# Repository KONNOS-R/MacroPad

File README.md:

Making a multipurpose Macro Pad for photo, video and audio editing for the blueprint "hackpad" project on hackclub.

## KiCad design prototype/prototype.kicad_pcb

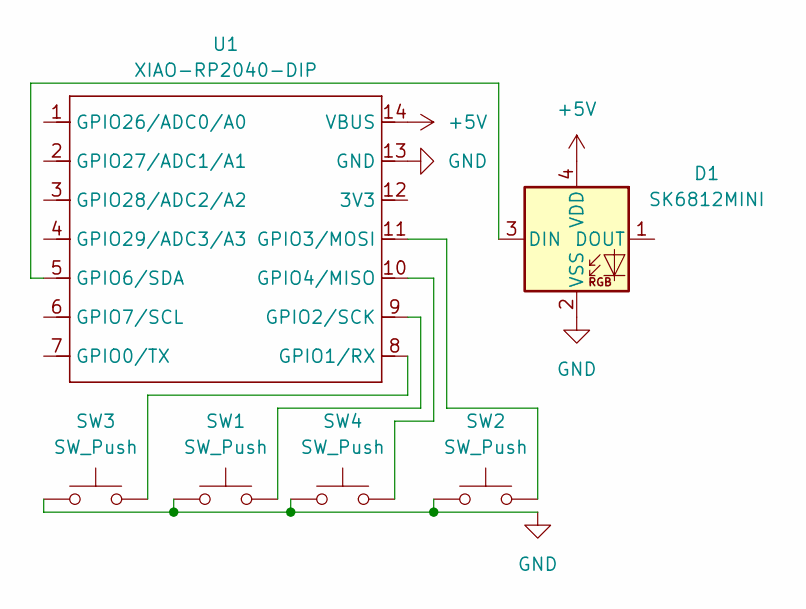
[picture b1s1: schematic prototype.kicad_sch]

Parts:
D1: SK6812MINI; LED_SK6812MINI_PLCC4_3.5x3.5mm_P1.75mm
SW1, SW2, SW3, SW4: SW_Push; SW_Cherry_MX_1.00u_PCB
U1: XIAO-RP2040-DIP

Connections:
+5V: D1.4 (VDD), U1.14 (VBUS)
GND: D1.2 (VSS), SW1.1, SW2.1, SW3.1, SW4.1, U1.13 (GND)
unnamed: D1.3 (DIN), U1.5 (GPIO6/SDA)
unnamed: SW3.2, U1.8 (GPIO1/RX)
unnamed: SW1.2, U1.9 (GPIO2/SCK)
unnamed: SW2.2, U1.11 (GPIO3/MOSI)
unnamed: SW4.2, U1.10 (GPIO4/MISO)

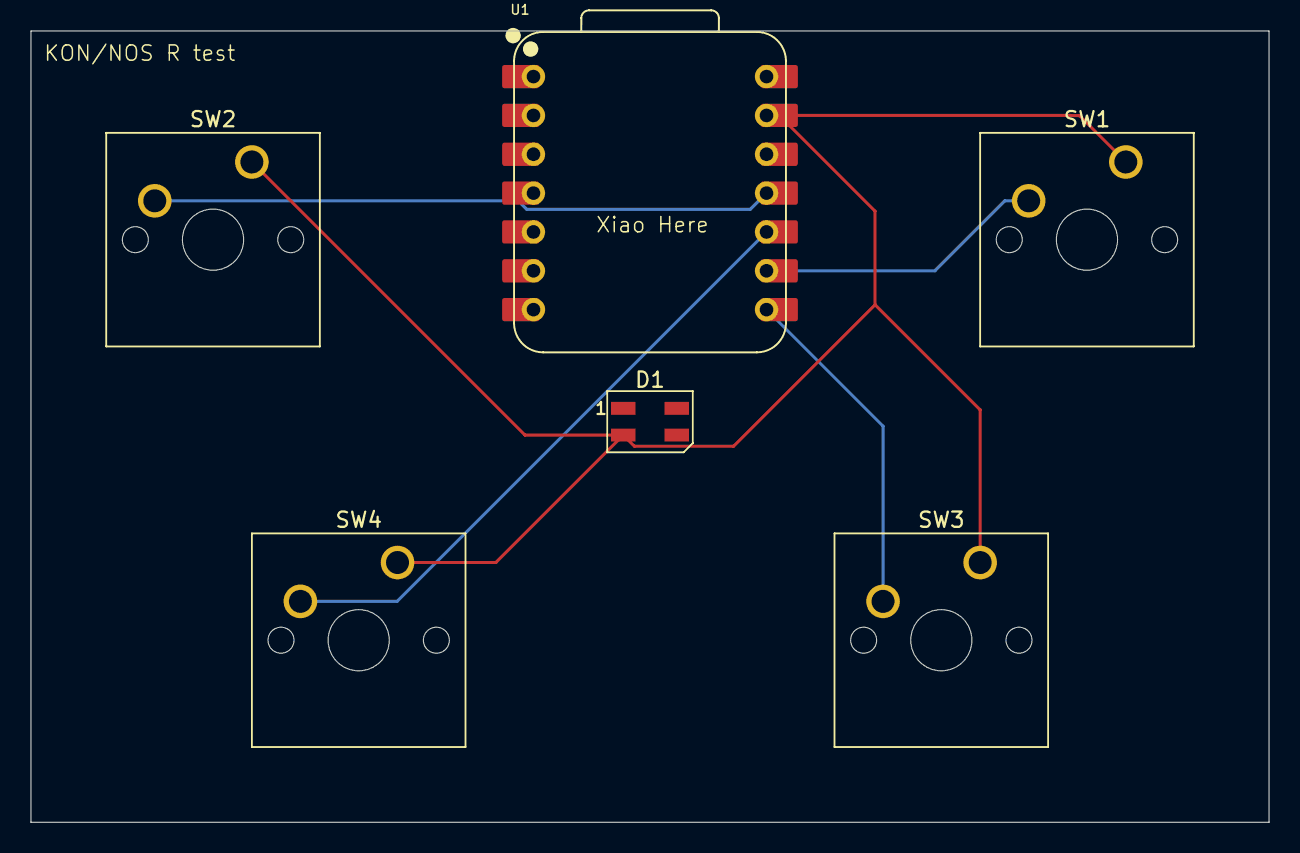
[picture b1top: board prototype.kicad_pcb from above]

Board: 2 copper layers, 81.0 x 51.7 mm, 6 parts (0 on the bottom side), 7 nets.
